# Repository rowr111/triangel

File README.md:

# Triangel!

ART!!! Made of 25 triangle tiles and 600 LEDs, for a wall or the corner of a room, with pleasing ambient patterns and exciting audio-reactive patterns specially tuned to follow music.

<table align="center">
  <tr>
    <td align="center"><br>Flame</td>
    <td align="center"><br>Uzumaki</td>
    <td align="center"><br>Fubuki</td>
    <td align="center"><br>Raindrop (sound)</td>
    <td align="center"><br>Spectrum (sound)</td>
  </tr>
</table>

- 50 cm per side when assembled
- 14 patterns: slow ambient ones, and ones that move with the beat, the drops and the shape of the music
- Audio-reactive mode: set on/off or auto-detected when music is playing
- Controlled by: buttons, a sound switch or a remote; no app/connected computer needed
- Open source: the circuit boards, the brackets and the firmware are all here, in Rust, on two [dabao](https://www.crowdsupply.com/baochip/dabao) boards using the [Baochip-1x](https://github.com/baochip/baochip-1x), running [Xous](https://github.com/betrusted-io/xous-core)

You don't need a Triangel to write patterns for it: one dabao board and a browser will do. [Start here](docs/tutorials/first-run.md).

## Why the name?

Each triangle tile has a stylized eye design in the middle.. After I decided to cover it in eyes, I was inspired by biblical angel descriptions to name it... triangle + angel = Triangel!

## Where to go

### If you have a Triangel

- [Use your Triangel](USER_GUIDE.md#controls): the controls
- [Update its firmware](docs/how-to/update-your-triangel.md)

### If you want to build your own

- [How to build a Triangel](docs/how-to/build-a-triangel.md): everything you need, and how to put it together
  - [How to manufacture the circuit boards](docs/how-to/manufacture-the-circuit-boards.md)
  - [How to order the six-way and three-way brackets](docs/how-to/order-the-brackets.md)
  - [How to order the frame](docs/how-to/order-the-frame.md)
  - [How to order the wall brackets](docs/how-to/order-the-wall-brackets.md)
  - [How to order the controller board enclosure](docs/how-to/order-the-controller-board-enclosure.md)
  - [Print the stickers and overlays](graphics/README.md)

### If you want to develop

- **Learn**
  - [Build and preview Triangel patterns with one dabao](docs/tutorials/first-run.md): start here if you are new, or don't have Triangel hardware
  - [Write your first pattern](docs/tutorials/first-pattern.md)
  - [Write a sound pattern](docs/tutorials/first-sound-pattern.md)
- **How to**
  - **Get set up**
    - [Set up your machine](docs/how-to/set-up-a-development-machine.md)
    - [Build the firmware and flash the boards](docs/how-to/build-and-flash.md)
    - [Make a dabao start by itself](docs/how-to/make-a-dabao-start-by-itself.md)
    - [Watch the patterns in a browser](docs/how-to/run-the-previewer.md)
  - **Work on patterns**
    - [Add a pattern](docs/how-to/add-a-pattern.md)
    - [Make a pattern fast enough](docs/how-to/make-a-pattern-fast-enough.md)
    - [Tune the sound response](docs/how-to/tune-the-sound-response.md)
  - **Hardware and the deeper parts**
    - [Check a microphone that is not working](docs/how-to/check-the-microphone.md)
    - [Change the microphone's pins](docs/how-to/regenerate-the-mic-program.md)
    - [Regenerate the LED map](docs/how-to/regenerate-the-led-map.md)
    - [Build the kernels](docs/how-to/build-the-kernels.md)
- **Understand**
  - [How Triangel works](docs/explanation/how-triangel-works.md): the parts, the two boards, a frame, the setlists and the kernel
  - [How sound becomes light](docs/explanation/how-sound-becomes-light.md): from the microphone, through the 24 bands, to beats and drops
- **Look things up**
  - [Pattern toolkit](docs/reference/pattern-toolkit.md): the helpers, the measurements and the sound
  - [Triangle tiles and wiring](docs/reference/triangle-tiles-and-wiring.md): the layout, the numbering and the two chains
  - [Pins](docs/reference/pins.md): which dabao pins each board uses
  - [The ear-to-eye link](docs/reference/ear-to-eye-link.md): the frames the ear sends, byte by byte
  - [Diagnostic output](docs/reference/diagnostic-output.md): the status lines the eye and the ear can print, for troubleshooting
  - [Contributing](CONTRIBUTING.md)

## What is in this repository

| Folder | Contents |
|---|---|
| [`firmware/eye/`](firmware/eye/) | The eye's firmware: LED output, patterns, controls |
| [`firmware/ear/`](firmware/ear/) | The ear's firmware: microphone, frequency bands, the link to the eye |
| [`firmware/shared/`](firmware/shared/) | Code both use: the format of what the ear sends, and the sound tuning |
| [`triangel-previewer/`](triangel-previewer/) | Shows the eye's LED output in a browser |
| [`hardware/`](hardware/) | The circuit boards (KiCad) and the brackets |
| [`graphics/`](graphics/README.md) | Artwork and the sticker sheets |

## License

MIT. See [LICENSE](LICENSE).

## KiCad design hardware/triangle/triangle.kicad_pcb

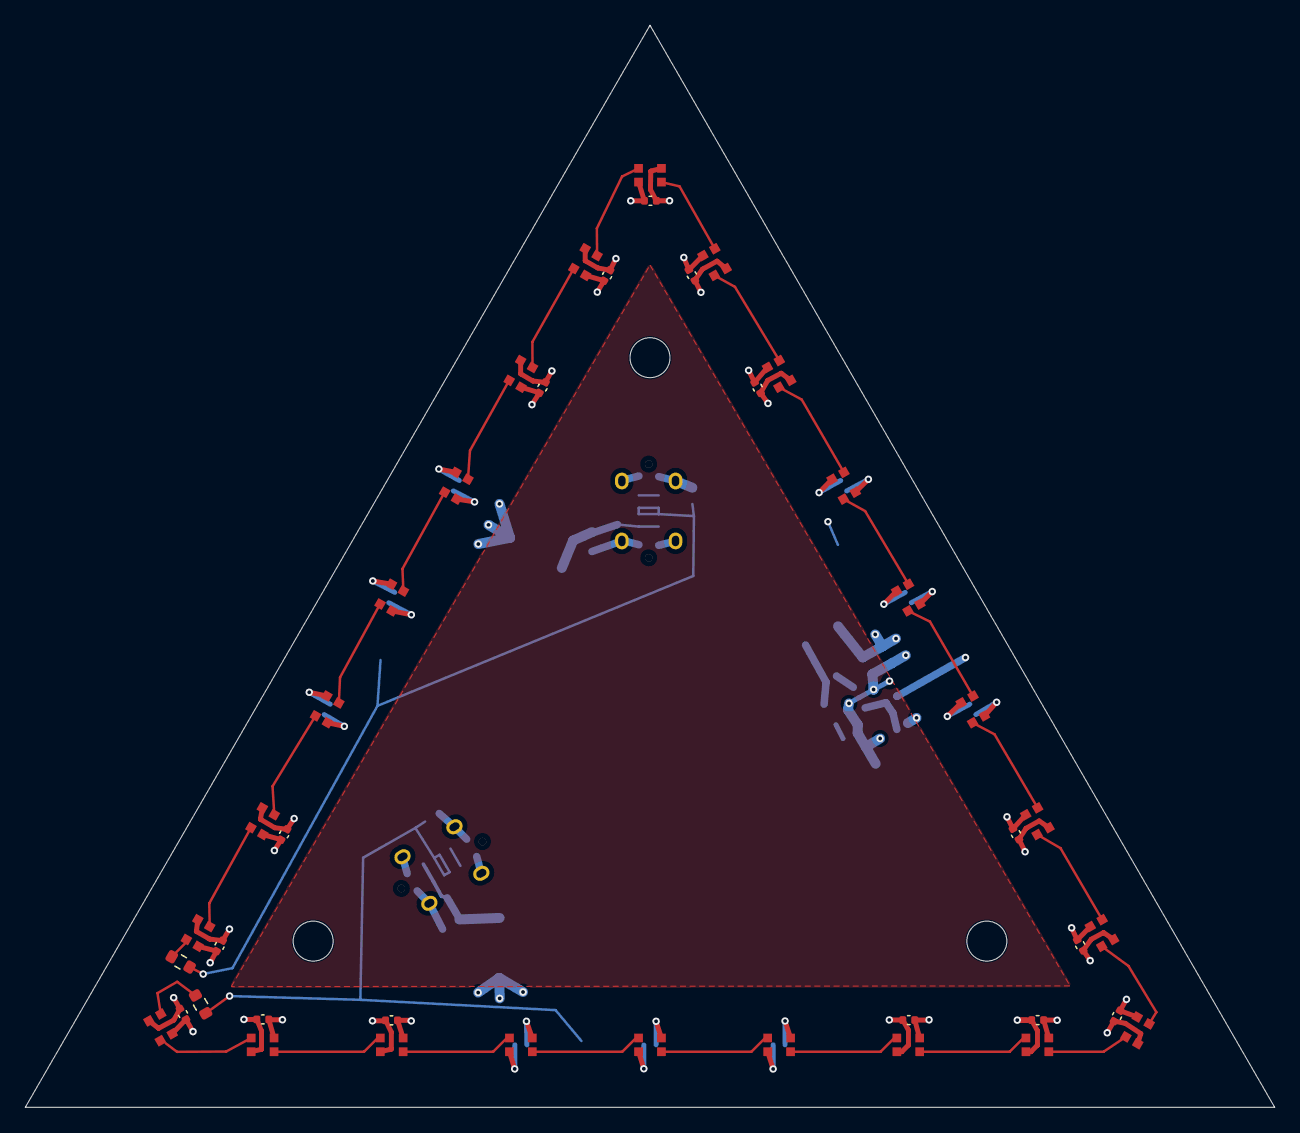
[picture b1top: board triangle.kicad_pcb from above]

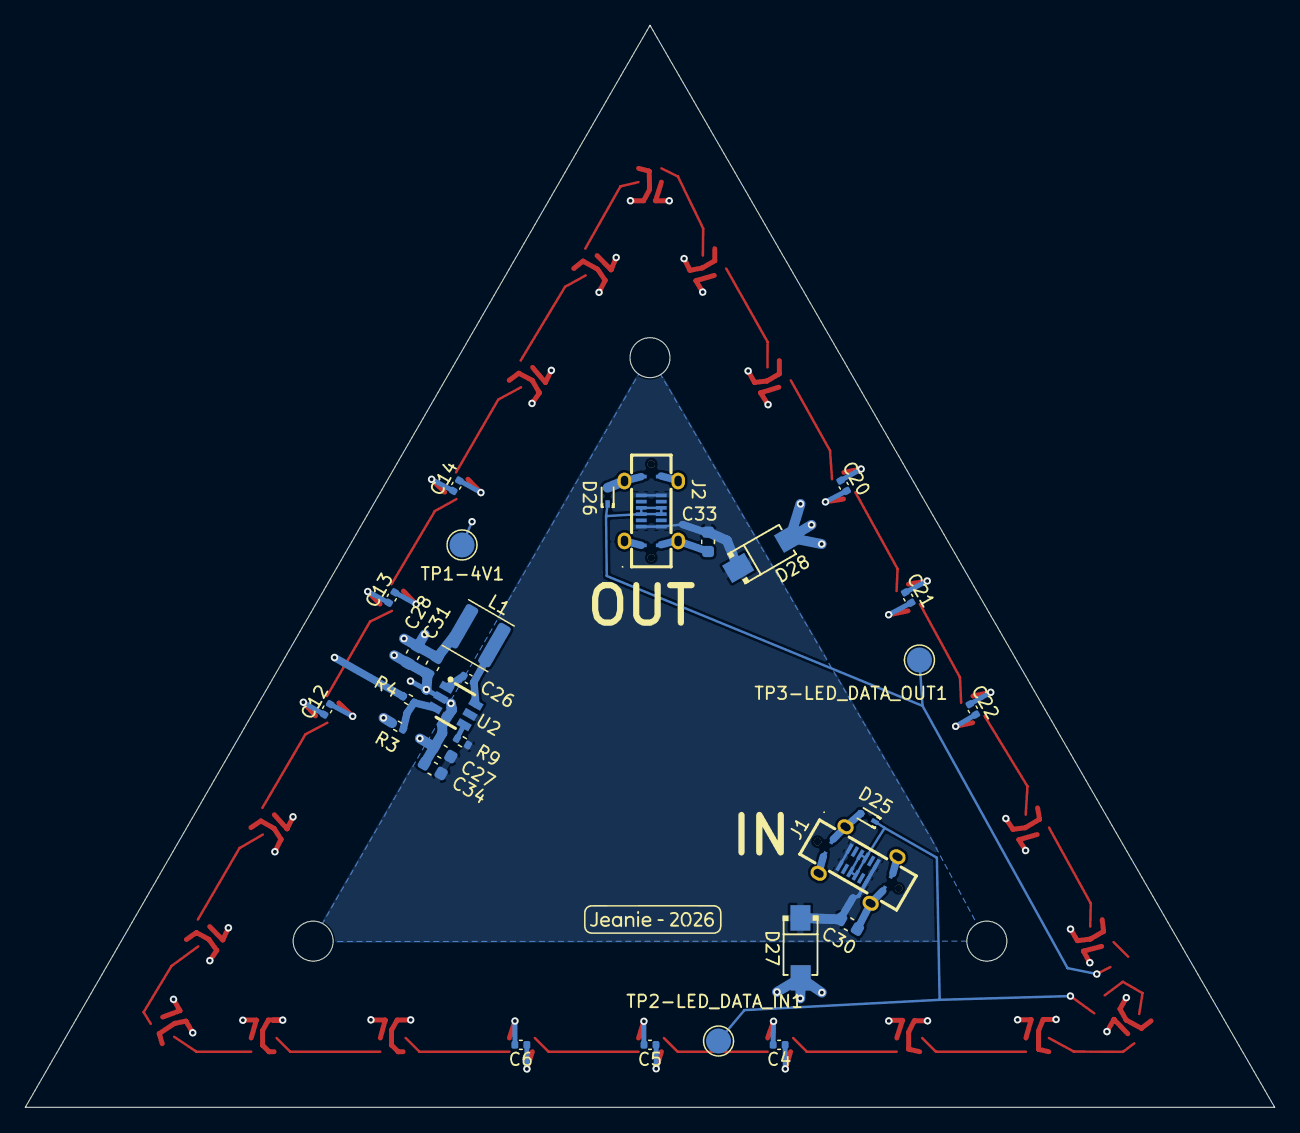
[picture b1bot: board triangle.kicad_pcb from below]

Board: 4 copper layers, 100.0 x 86.6 mm, 74 parts (30 on the bottom side), 34 nets.

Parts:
C1, C2, C3, C4, C5, C6, C7, C8, C9, C10, C11, C12, C13, C14, C15, C16, C17, C18, C19, C20, C21, C22, C23, C24: 100nF; C_0402_1005Metric
C26: 33nF; C_0402_1005Metric
C27, C28, C30, C31, C33, C34: 10µF; C_0603_1608Metric
D1, D2, D3, D4, D5, D6, D7, D8, D9, D10, D11, D12, D13, D14, D15, D16, D17, D18, D19, D20, D21, D22, D23, D24: WS2812B-2020; LED_WS2812B-2020_PLCC4_2.0x2.0mm - no silkscreen
D25, D26: H5VUD5U_C20617921; SOD-523_L1.2-W0.8-LS1.6-RD
D27, D28: SMAJ15A_C19077535; SMA_L4.3-W2.6-LS5.0-RD
H1, H2, H3: MountingHole; MountingHole_3.2mm_M3
J1, J2: USB_C_Receptacle_USB2.0_16P; TYPE-C-SMD_USB4120-03-C
L1: 4.7uH; L_Changjiang_FNR4030S
R1, R2: 33Ω; R_0603_1608Metric
R3, R9: 100kΩ; R_0402_1005Metric
R4: 560kΩ; R_0402_1005Metric
TP1-4V1, TP2-LED_DATA_IN1, TP3-LED_DATA_OUT1: TestPoint; TestPoint_Pad_D2.0mm
U2: EA8212HT6R; SOT-23-6_L2.9-W1.6-P0.95-LS2.8-BR

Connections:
+4V: C1.1, C2.1, C3.1, C4.1, C5.1, C6.1, C7.1, C8.1, C9.1, C10.1, C11.1, C12.1, C13.1, C14.1, C15.1, C16.1, C17.1, C18.1, C19.1, C20.1, C21.1, C22.1, C23.1, C24.1, C28.1, C31.1, D1.4 (VDD), D2.4 (VDD), D3.4 (VDD), D4.4 (VDD), D5.4 (VDD), D6.4 (VDD), D7.4 (VDD), D8.4 (VDD), D9.4 (VDD), D10.4 (VDD), D11.4 (VDD), D12.4 (VDD), D13.4 (VDD), D14.4 (VDD), D15.4 (VDD), D16.4 (VDD), D17.4 (VDD), D18.4 (VDD), D19.4 (VDD), D20.4 (VDD), D21.4 (VDD), D22.4 (VDD), D23.4 (VDD), D24.4 (VDD), L1.2, R4.2, TP1-4V1.1 (1_1)
+12V: C27.1, C30.1, C33.1, C34.1, D27.1 (K), D28.1 (K), J1.A4 (VBUS), J1.A9 (VBUS), J1.B4 (VBUS), J1.B9 (VBUS), J2.A4 (VBUS), J2.A9 (VBUS), J2.B4 (VBUS), J2.B9 (VBUS), R9.2, U2.5 (PWR)
GND: C1.2, C2.2, C3.2, C4.2, C5.2, C6.2, C7.2, C8.2, C9.2, C10.2, C11.2, C12.2, C13.2, C14.2, C15.2, C16.2, C17.2, C18.2, C19.2, C20.2, C21.2, C22.2, C23.2, C24.2, C27.2, C28.2, C30.2, C31.2, C33.2, C34.2, D1.2 (VSS), D2.2 (VSS), D3.2 (VSS), D4.2 (VSS), D5.2 (VSS), D6.2 (VSS), D7.2 (VSS), D8.2 (VSS), D9.2 (VSS), D10.2 (VSS), D11.2 (VSS), D12.2 (VSS), D13.2 (VSS), D14.2 (VSS), D15.2 (VSS), D16.2 (VSS), D17.2 (VSS), D18.2 (VSS), D19.2 (VSS), D20.2 (VSS), D21.2 (VSS), D22.2 (VSS), D23.2 (VSS), D24.2 (VSS), D25.2 (A), D26.2 (A), D27.2 (A), D28.2 (A), J1.0 (EH), J1.A1 (GND), J1.A12 (GND), J1.B1 (GND), J1.B12 (GND), J2.0 (EH), J2.A1 (GND), J2.A12 (GND), J2.B1 (GND), J2.B12 (GND), R3.2, U2.2 (GND)
LED_DATA_IN: D25.1 (C), J1.A6 (DP1), J1.A7 (DN1), J1.B6 (DP2), J1.B7 (DN2), R1.1, TP2-LED_DATA_IN1.1 (1_1)
LED_DATA_OUT: D26.1 (C), J2.A6 (DP1), J2.A7 (DN1), J2.B6 (DP2), J2.B7 (DN2), R2.2, TP3-LED_DATA_OUT1.1 (1_1)
unnamed: D1.3 (DIN), R1.2
unnamed: D1.1 (DOUT), D2.3 (DIN)
unnamed: D2.1 (DOUT), D3.3 (DIN)
unnamed: D3.1 (DOUT), D4.3 (DIN)
unnamed: D4.1 (DOUT), D5.3 (DIN)
unnamed: D5.1 (DOUT), D6.3 (DIN)
unnamed: D6.1 (DOUT), D7.3 (DIN)
unnamed: D7.1 (DOUT), D8.3 (DIN)
unnamed: D8.1 (DOUT), D9.3 (DIN)
unnamed: D9.1 (DOUT), D10.3 (DIN)
unnamed: D10.1 (DOUT), D11.3 (DIN)
unnamed: D11.1 (DOUT), D12.3 (DIN)
unnamed: D12.1 (DOUT), D13.3 (DIN)
unnamed: D13.1 (DOUT), D14.3 (DIN)
unnamed: D14.1 (DOUT), D15.3 (DIN)
unnamed: D15.1 (DOUT), D16.3 (DIN)
unnamed: D16.1 (DOUT), D17.3 (DIN)
unnamed: D17.1 (DOUT), D18.3 (DIN)
unnamed: D18.1 (DOUT), D19.3 (DIN)
unnamed: D19.1 (DOUT), D20.3 (DIN)
unnamed: D20.1 (DOUT), D21.3 (DIN)
unnamed: D21.1 (DOUT), D22.3 (DIN)
unnamed: D22.1 (DOUT), D23.3 (DIN)
unnamed: D23.1 (DOUT), D24.3 (DIN)
unnamed: D24.1 (DOUT), R2.1
unnamed: C26.1, U2.1 (BOOT)
unnamed: R3.1, R4.1, U2.3 (FBK)
unnamed: R9.1, U2.4 (RUN)
unnamed: C26.2, L1.1, U2.6 (SWITCH)

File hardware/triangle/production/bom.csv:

Designator,Footprint,Quantity,Value,LCSC Part #
"C1, C10, C11, C12, C13, C14, C15, C16, C17, C18, C19, C2, C20, C21, C22, C23, C24, C3, C4, C5, C6, C7, C8, C9",0402,24,100nF,C1525
C26,0402,1,33nF,C507072
"C27, C28, C30, C31, C33, C34",0603,6,10µF,C96446
"D1, D10, D11, D12, D13, D14, D15, D16, D17, D18, D19, D2, D20, D21, D22, D23, D24, D3, D4, D5, D6, D7, D8, D9",LED_WS2812B-2020_PLCC4_2.0x2.0mm - no silkscreen,24,WS2812B-2020,C52917434
"D25, D26",SOD-523_L1.2-W0.8-LS1.6-RD,2,H5VUD5U_C20617921,C20617921
"D27, D28",SMA_L4.3-W2.6-LS5.0-RD,2,SMAJ15A_C19077535,C19077535
"J1, J2",TYPE-C-SMD_USB4120-03-C,2,USB_C_Receptacle_USB2.0_16P,C3151749
L1,L_Changjiang_FNR4030S,1,4.7uH,C167874
"R1, R2",0603,2,33Ω,C23140
"R3, R9",0402,2,100kΩ,C60491
R4,0402,1,560kΩ,C132339
U2,SOT-23-6_L2.9-W1.6-P0.95-LS2.8-BR,1,EA8212HT6R,C609568

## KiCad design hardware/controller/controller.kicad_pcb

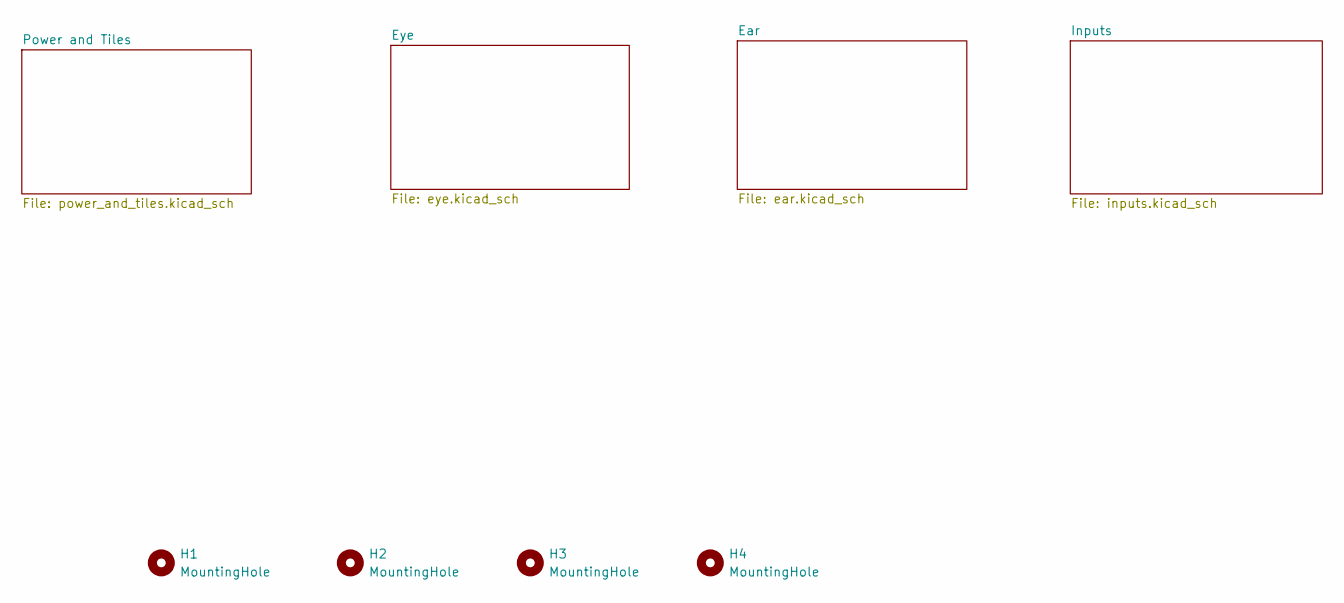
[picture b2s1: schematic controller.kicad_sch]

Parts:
H1, H2, H3, H4: MountingHole; MountingHole_3.2mm_M3_Pad

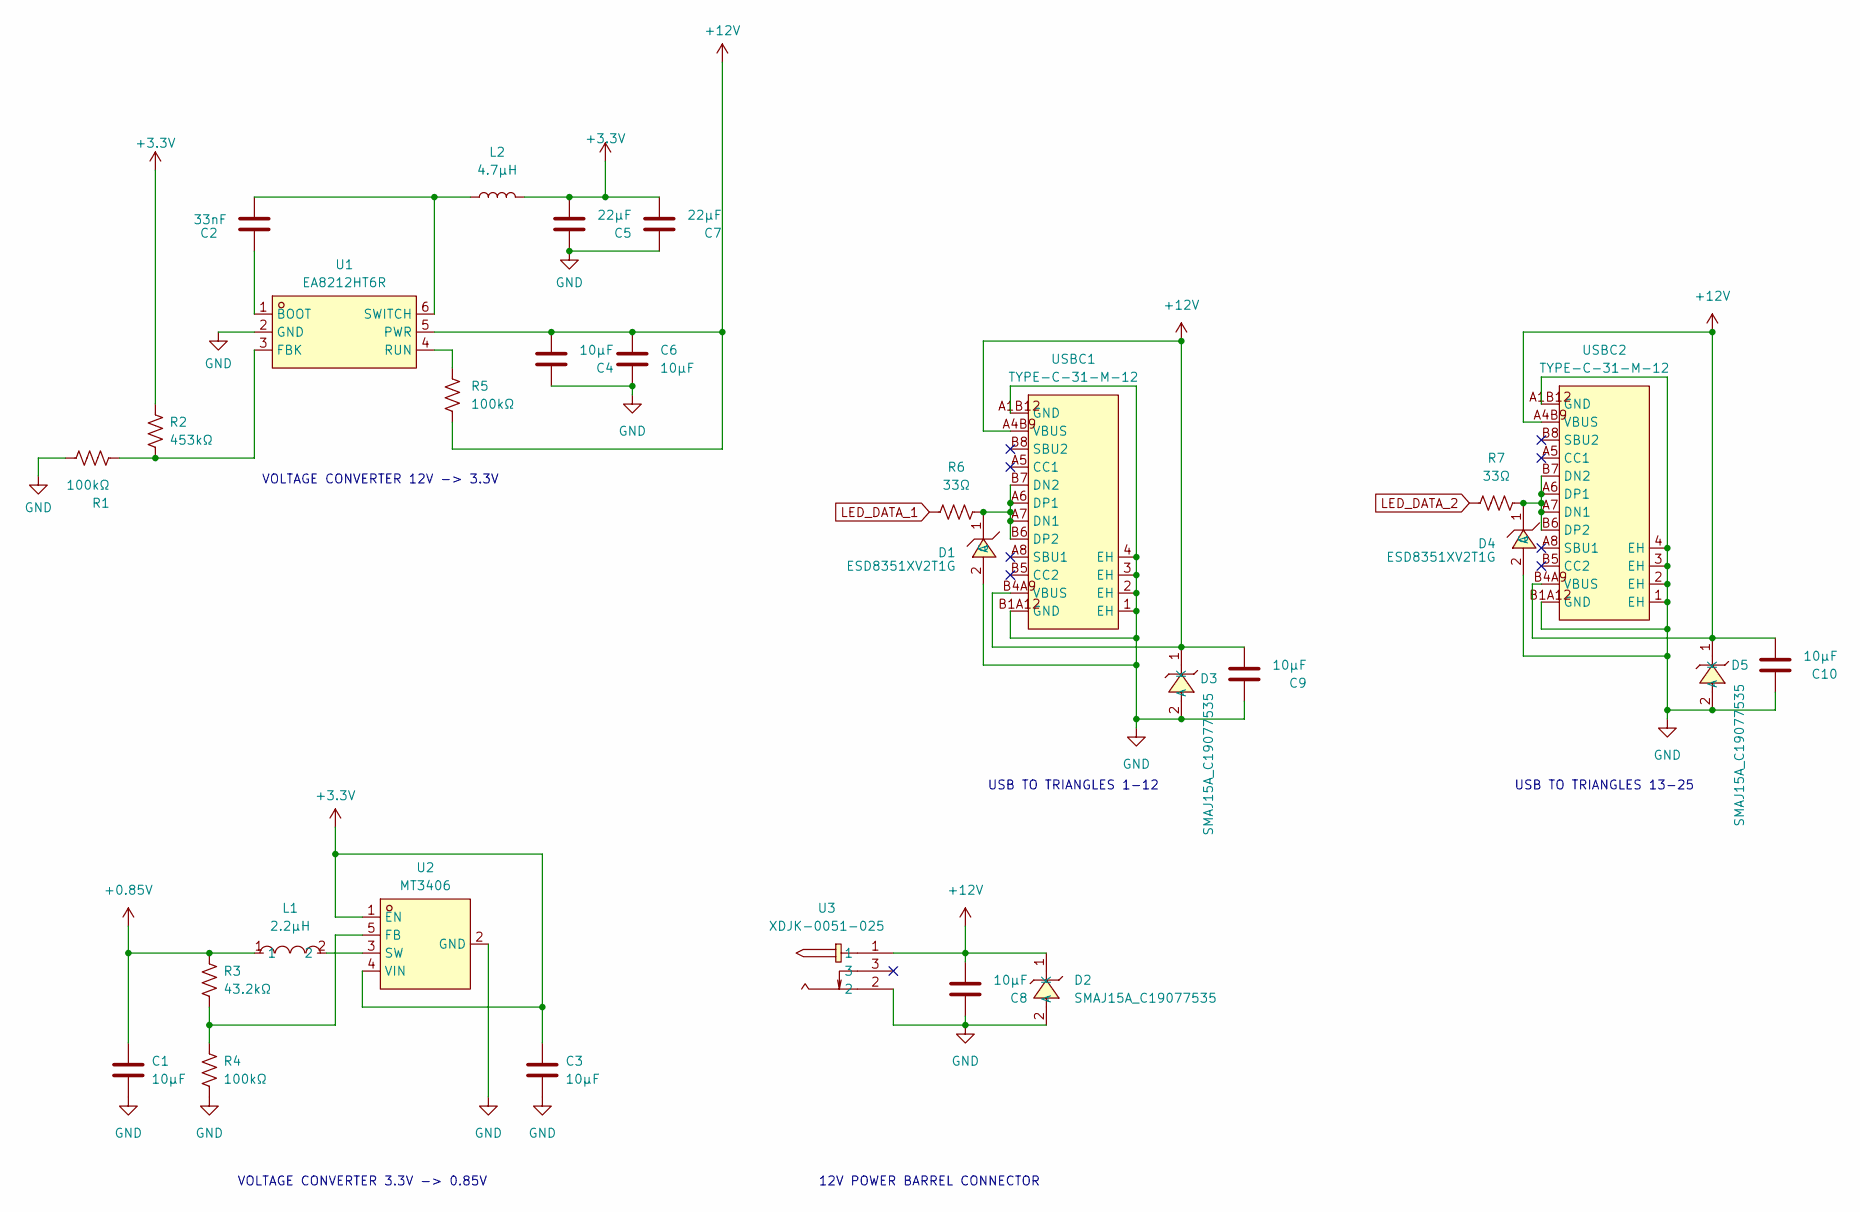
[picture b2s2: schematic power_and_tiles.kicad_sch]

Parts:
C1, C3, C4, C6, C8, C9, C10: 10µF; C_0603_1608Metric; LCSC Part C96446
C2: 33nF; C_0402_1005Metric; LCSC Part C507072
C5, C7: 22µF; C_0805_2012Metric; LCSC Part C45783
D1, D4: ESD8351XV2T1G; SOD-523_L1.2-W0.8-LS1.6-RD; MPN ESD8351XV2T1G; LCSC Part C19829478
D2, D3, D5: SMAJ15A_C19077535; SMA_L4.3-W2.6-LS5.0-RD; MPN SMAJ15A; LCSC Part C19077535
L1: 2.2µH; L0805; MPN MGFL2012F2R2MT-LF; LCSC Part C281115
L2: 4.7µH; L_Changjiang_FNR4030S; MPN FNR4030S4R7MT; LCSC Part C167874
R1, R4, R5: 100kΩ; R_0402_1005Metric; LCSC Part C60491
R2: 453kΩ; R_0402_1005Metric; LCSC Part C27009
R3: 43.2kΩ; R_0402_1005Metric; LCSC Part C25894
R6, R7: 33Ω; R_0402_1005Metric; LCSC Part C25105
U1: EA8212HT6R; SOT-23-6_L2.9-W1.6-P0.95-LS2.8-BR; MPN EA8212HT6R; LCSC Part C609568
U2: MT3406; SOT-23-5; MPN MT3406; LCSC Part C22462728
U3: XDJK-0051-025; DC-IN-TH_XDJK-0051-025; MPN XDJK-0051-025; LCSC Part C7498153
USBC1, USBC2: TYPE-C-31-M-12; USB-C_SMD-TYPE-C-31-M-12_1; MPN TYPE-C-31-M-12; LCSC Part C165948

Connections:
+0.85V: C1.1, L1.1, R3.1; also elsewhere on the board
+3.3V: C3.1, C5.1, C7.1, L2.2, R2.2, U2.1 (EN), U2.4 (VIN); also elsewhere on the board
+12V: C4.1, C6.1, C8.1, C9.1, C10.1, D2.1 (K), D3.1 (K), D5.1 (K), R5.2, U1.5 (PWR), U3.1, USBC1.A4B9 (VBUS), USBC1.B4A9 (VBUS), USBC2.A4B9 (VBUS), USBC2.B4A9 (VBUS)
GND: C1.2, C3.2, C4.2, C5.2, C6.2, C7.2, C8.2, C9.2, C10.2, D1.2 (A), D2.2 (A), D3.2 (A), D4.2 (A), D5.2 (A), R1.2, R4.2, U1.2 (GND), U2.2 (GND), U3.2, USBC1.1 (EH), USBC1.2 (EH), USBC1.3 (EH), USBC1.4 (EH), USBC1.A1B12 (GND), USBC1.B1A12 (GND), USBC2.1 (EH), USBC2.2 (EH), USBC2.3 (EH), USBC2.4 (EH), USBC2.A1B12 (GND), USBC2.B1A12 (GND); also elsewhere on the board
LED_DATA_1: R6.1; also elsewhere on the board
LED_DATA_2: R7.1; also elsewhere on the board
unnamed: D1.1 (C), R6.2, USBC1.A6 (DP1), USBC1.A7 (DN1), USBC1.B6 (DP2), USBC1.B7 (DN2)
unnamed: D4.1 (C), R7.2, USBC2.A6 (DP1), USBC2.A7 (DN1), USBC2.B6 (DP2), USBC2.B7 (DN2)
unnamed: C2.1, U1.1 (BOOT)
unnamed: R1.1, R2.1, U1.3 (FBK)
unnamed: R5.1, U1.4 (RUN)
unnamed: C2.2, L2.1, U1.6 (SWITCH)
unnamed: R3.2, R4.1, U2.5 (FB)
unnamed: L1.2, U2.3 (SW)

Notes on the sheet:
USB TO TRIANGLES 13-25
VOLTAGE CONVERTER 3.3V -> 0.85V
12V POWER BARREL CONNECTOR
VOLTAGE CONVERTER 12V -> 3.3V
USB TO TRIANGLES 1-12

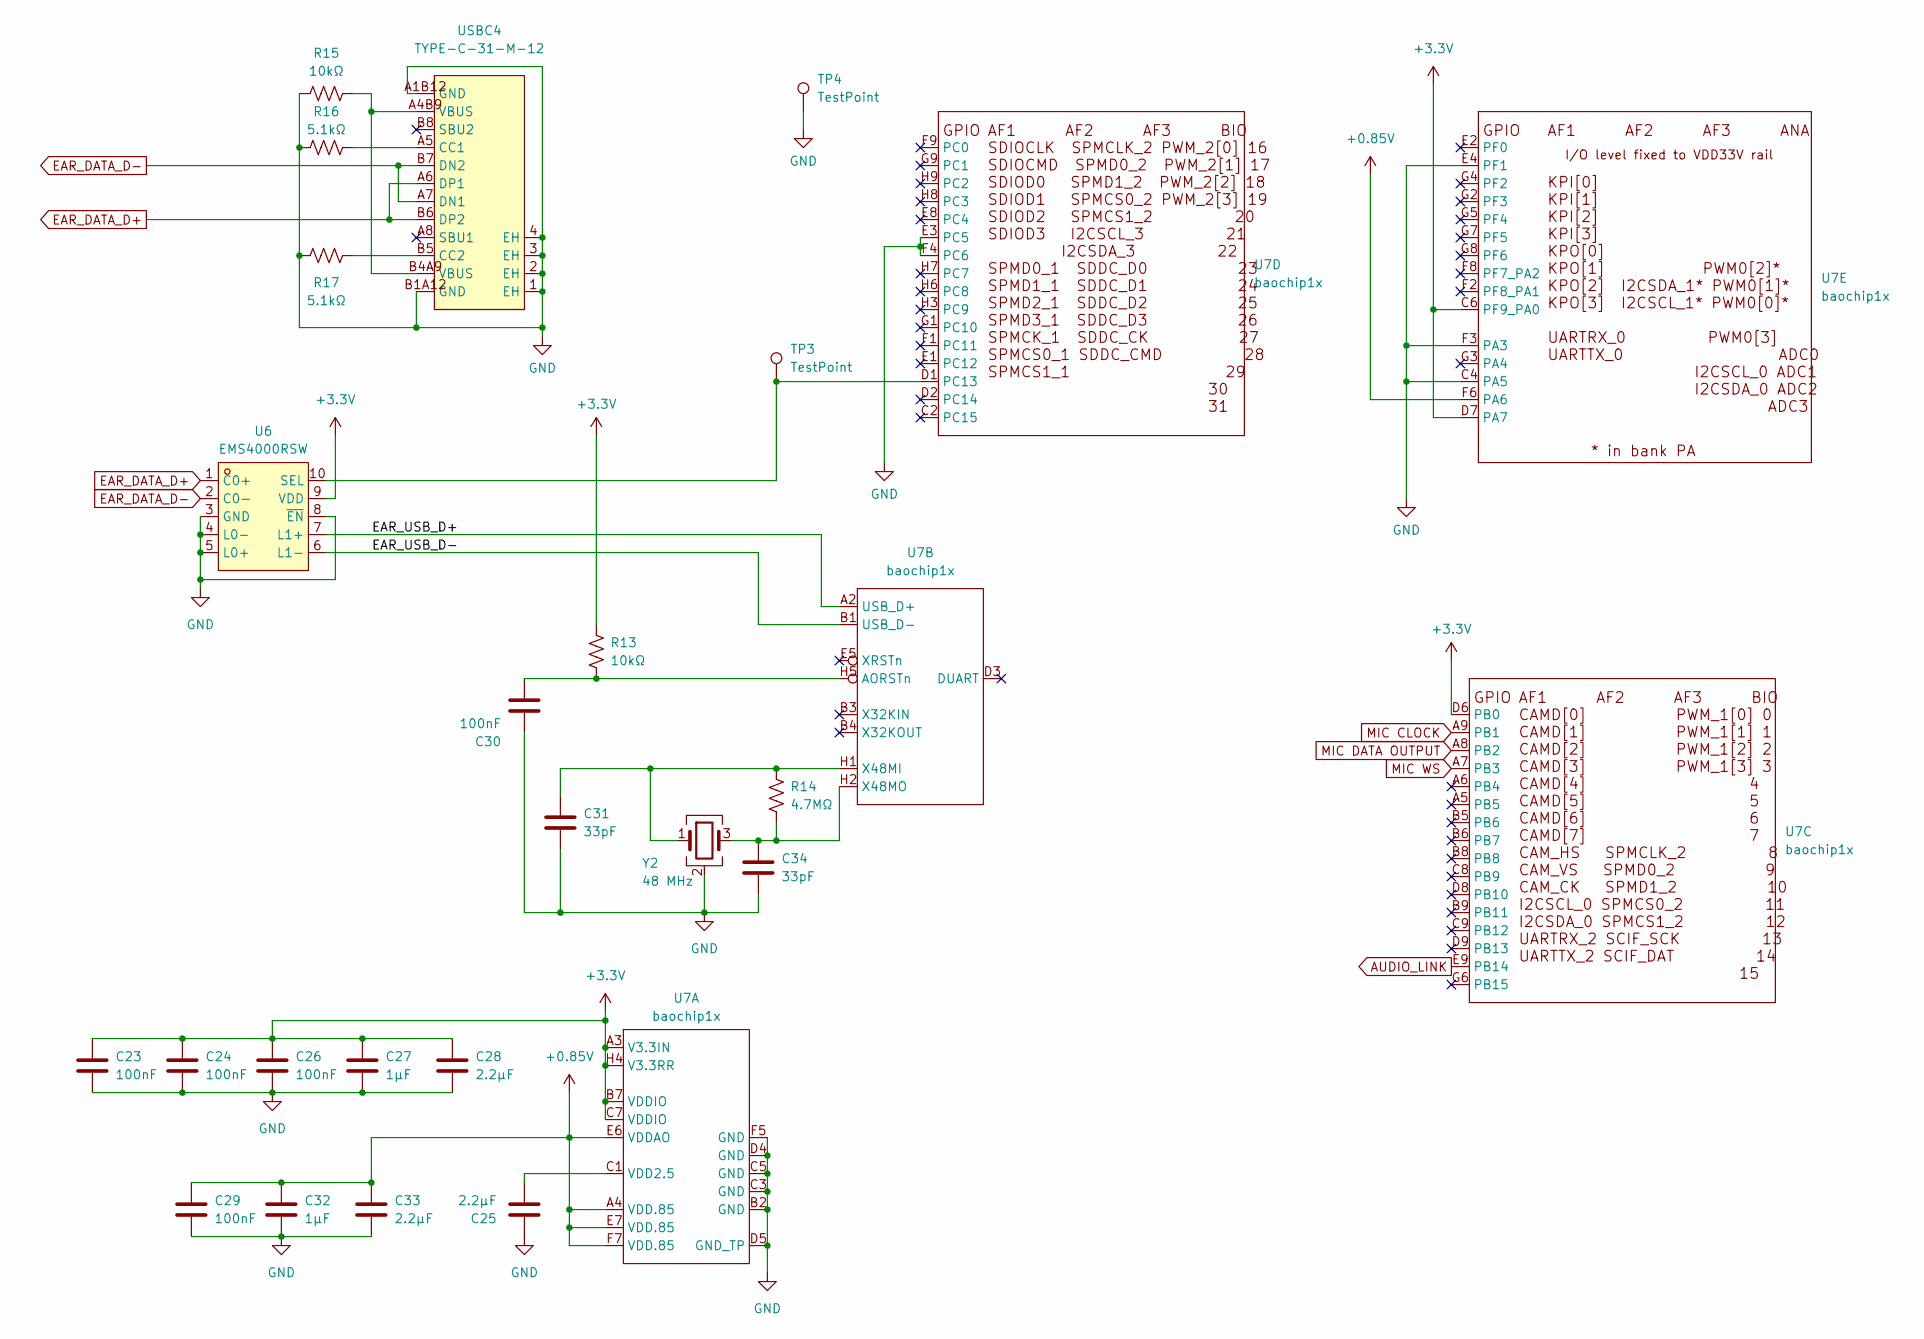
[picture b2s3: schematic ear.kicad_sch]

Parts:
C23, C24, C26, C29, C30: 100nF; C_0201_0603Metric; LCSC Part C76934
C25, C28, C33: 2.2µF; C_0201_0603Metric; LCSC Part C76933
C27, C32: 1µF; C_0201_0603Metric; LCSC Part C76935
C31, C34: 33pF; C_0201_0603Metric; LCSC Part C56903
R13: 10kΩ; R_0201_0603Metric; LCSC Part C106225
R14: 4.7MΩ; R_0402_1005Metric; LCSC Part C474132
R15: 10kΩ; R_0402_1005Metric; LCSC Part C25744
R16, R17: 5.1kΩ; R_0402_1005Metric; LCSC Part C25905
TP3, TP4: TestPoint; TestPoint_Pad_D1.0mm
U6: EMS4000RSW; UQFN-10_L1.8-W1.4-P0.40-TL; MPN EMS4000RSW; LCSC Part C49186227
U7: baochip1x; WLCSP-71_9x8_4.062x3.762mm
USBC4: TYPE-C-31-M-12; USB-C_SMD-TYPE-C-31-M-12_1; MPN TYPE-C-31-M-12; LCSC Part C165948
Y2: 48 MHz; Crystal_SMD_3225-4Pin_3.2x2.5mm; LCSC Part C2892060

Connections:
+0.85V: C29.1, C32.1, C33.1, U7.A4 (VDD.85), U7.E6 (VDDAO), U7.E7 (VDD.85), U7.F6 (PA6), U7.F7 (VDD.85); also elsewhere on the board
+3.3V: C23.1, C24.1, C26.1, C27.1, C28.1, R13.1, U6.9 (VDD), U7.A3 (V3.3IN), U7.B7 (VDDIO), U7.C6 (PF9_PA0), U7.C7 (VDDIO), U7.D6 (PB0), U7.D7 (PA7), U7.H4 (V3.3RR); also elsewhere on the board
/Ear/EAR_RX: U7.D9 (PB13); also elsewhere on the board
/Ear/EAR_USB_D+: U6.7 (L1+), U7.A2 (USB_D+)
/Ear/EAR_USB_D-: U6.6 (L1-), U7.B1 (USB_D-)
AUDIO_LINK: U7.E9 (PB14); also elsewhere on the board
EAR_DATA_D+: U6.1 (C0+), USBC4.A6 (DP1), USBC4.B6 (DP2)
EAR_DATA_D-: U6.2 (C0-), USBC4.A7 (DN1), USBC4.B7 (DN2)
GND: C23.2, C24.2, C25.2, C26.2, C27.2, C28.2, C29.2, C30.2, C31.2, C32.2, C33.2, C34.2, R15.1, R16.1, R17.1, TP4.1, U6.3 (GND), U6.4 (L0-), U6.5 (L0+), U6.8 (~EN), U7.B2 (GND), U7.C3 (GND), U7.C4 (PA5), U7.C5 (GND), U7.D4 (GND), U7.D5 (GND_TP), U7.E3 (PC5), U7.E4 (PF1), U7.F3 (PA3), U7.F4 (PC6), U7.F5 (GND), USBC4.1 (EH), USBC4.2 (EH), USBC4.3 (EH), USBC4.4 (EH), USBC4.A1B12 (GND), USBC4.B1A12 (GND), Y2.2 (G), Y2.4 (G); also elsewhere on the board
MIC CLOCK: U7.A9 (PB1); also elsewhere on the board
MIC DATA OUTPUT: U7.A8 (PB2); also elsewhere on the board
MIC WS: U7.A7 (PB3); also elsewhere on the board
unnamed: R15.2, USBC4.A4B9 (VBUS), USBC4.B4A9 (VBUS)
unnamed 36: TP3.1, U6.10 (SEL), U7.D1 (PC13); also elsewhere on the board
unnamed: C25.1, U7.C1 (VDD2.5)
unnamed 48: C30.1, R13.2, U7.H5 (AORSTn); also elsewhere on the board
unnamed: C31.1, R14.1, U7.H1 (X48MI), Y2.1
unnamed: C34.1, R14.2, U7.H2 (X48MO), Y2.3
unnamed: R16.2, USBC4.A5 (CC1)
unnamed: R17.2, USBC4.B5 (CC2)

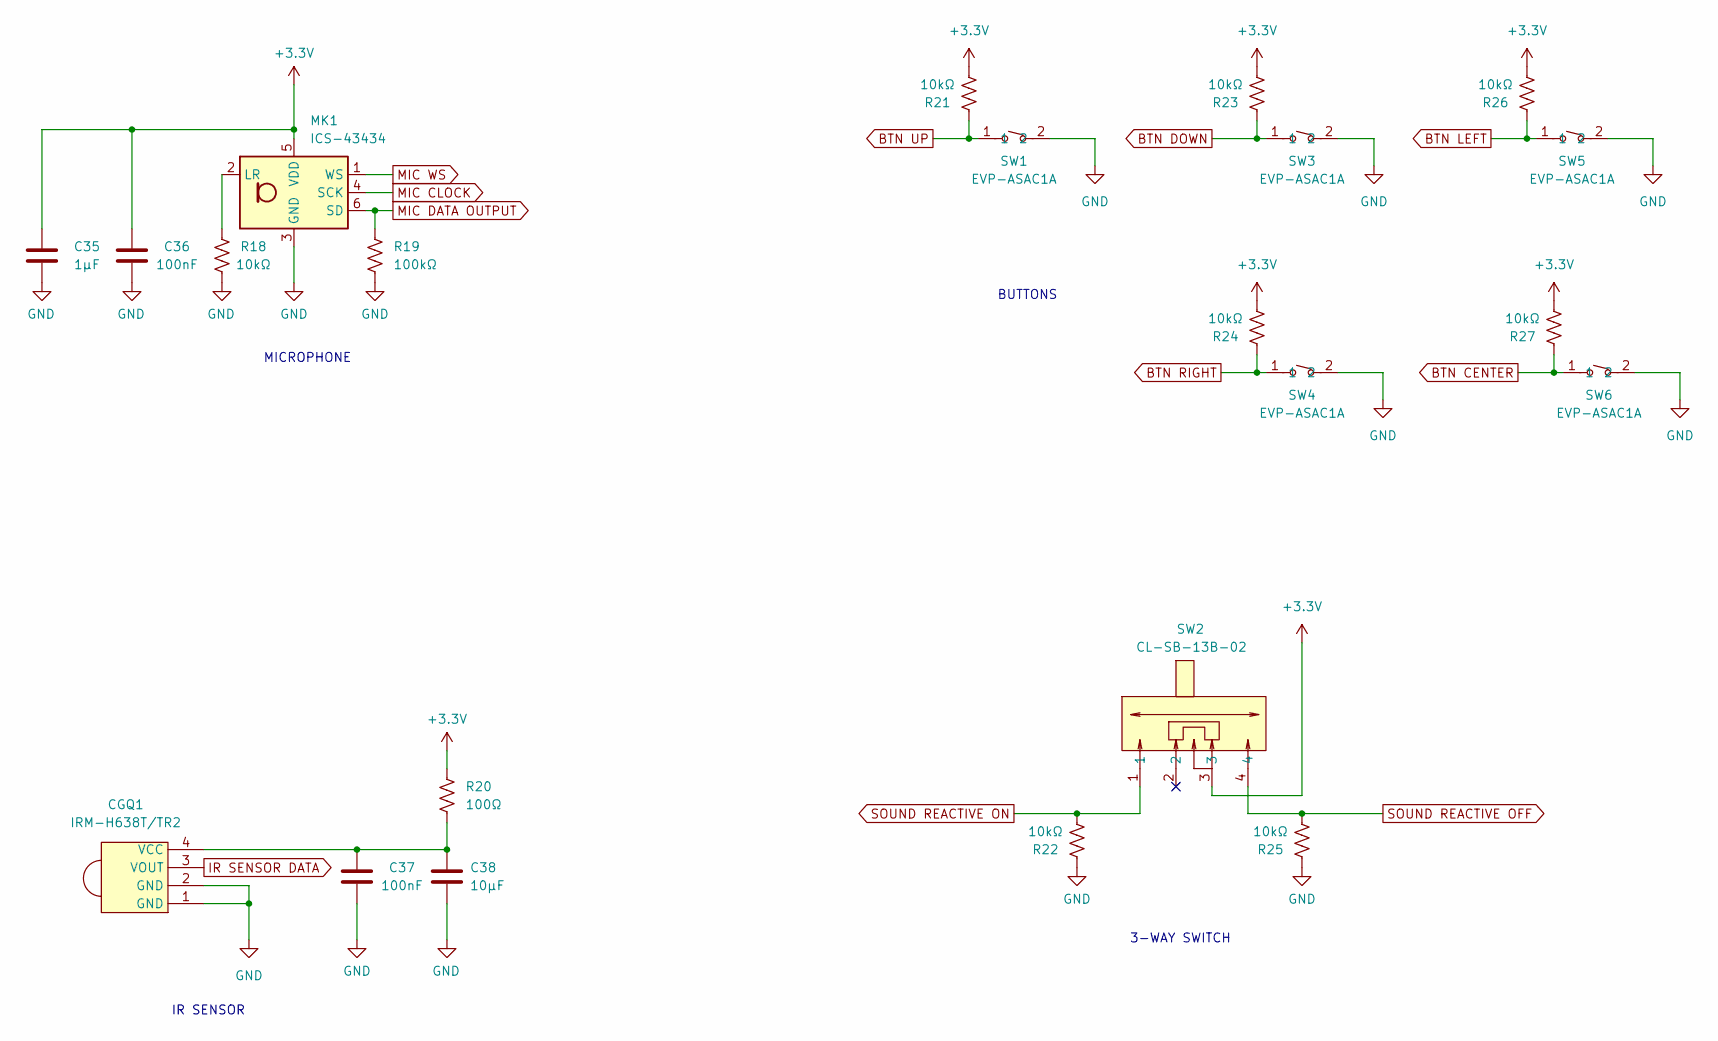
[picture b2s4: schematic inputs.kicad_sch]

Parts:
C35: 1µF; C_0402_1005Metric; LCSC Part C52923
C36, C37: 100nF; C_0402_1005Metric; LCSC Part C1525
C38: 10µF; C_0402_1005Metric; LCSC Part C15525
CGQ1: IRM-H638T/TR2; SENSOR-SMD_IRM-H638T-TR2-TL; MPN IRM-H638T/TR2; LCSC Part C91447
MK1: ICS-43434; InvenSense_ICS-43434-6_3.5x2.65mm; LCSC Part C5656610
R18, R21, R22, R23, R24, R25, R26, R27: 10kΩ; R_0402_1005Metric; LCSC Part C25744
R19: 100kΩ; R_0402_1005Metric; LCSC Part C60491
R20: 100Ω; R_0402_1005Metric; LCSC Part C25076
SW1, SW3, SW4, SW5, SW6: EVP-ASAC1A; SW-SMD_PANASONIC_EVPASXXX; MPN EVP-ASAC1A; LCSC Part C4365033
SW2: CL-SB-13B-02; SW-SMD_NIDEC_CL-SB-13B-01T; MPN CL-SB-13B-02; LCSC Part C5596339

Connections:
+3.3V: C35.1, C36.1, MK1.5 (VDD), R20.2, R21.1, R23.1, R24.1, R26.1, R27.1, SW2.3; also elsewhere on the board
BTN CENTER: R27.2, SW6.1; also elsewhere on the board
BTN DOWN: R23.2, SW3.1; also elsewhere on the board
BTN LEFT: R26.2, SW5.1; also elsewhere on the board
BTN RIGHT: R24.2, SW4.1; also elsewhere on the board
BTN UP: R21.2, SW1.1; also elsewhere on the board
GND: C35.2, C36.2, C37.2, C38.1, CGQ1.1 (GND), CGQ1.2 (GND), MK1.3 (GND), R18.1, R19.1, R22.2, R25.2, SW1.2, SW3.2, SW4.2, SW5.2, SW6.2; also elsewhere on the board
IR SENSOR DATA: CGQ1.3 (VOUT); also elsewhere on the board
MIC CLOCK: MK1.4 (SCK); also elsewhere on the board
MIC DATA OUTPUT: MK1.6 (SD), R19.2; also elsewhere on the board
MIC WS: MK1.1 (WS); also elsewhere on the board
unnamed: C37.1, C38.2, CGQ1.4 (VCC), R20.1
unnamed: MK1.2 (LR), R18.2
SOUND REACTIVE OFF: R25.1, SW2.4; also elsewhere on the board
SOUND REACTIVE ON: R22.1, SW2.1; also elsewhere on the board

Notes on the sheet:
MICROPHONE
IR SENSOR
BUTTONS
3-WAY SWITCH

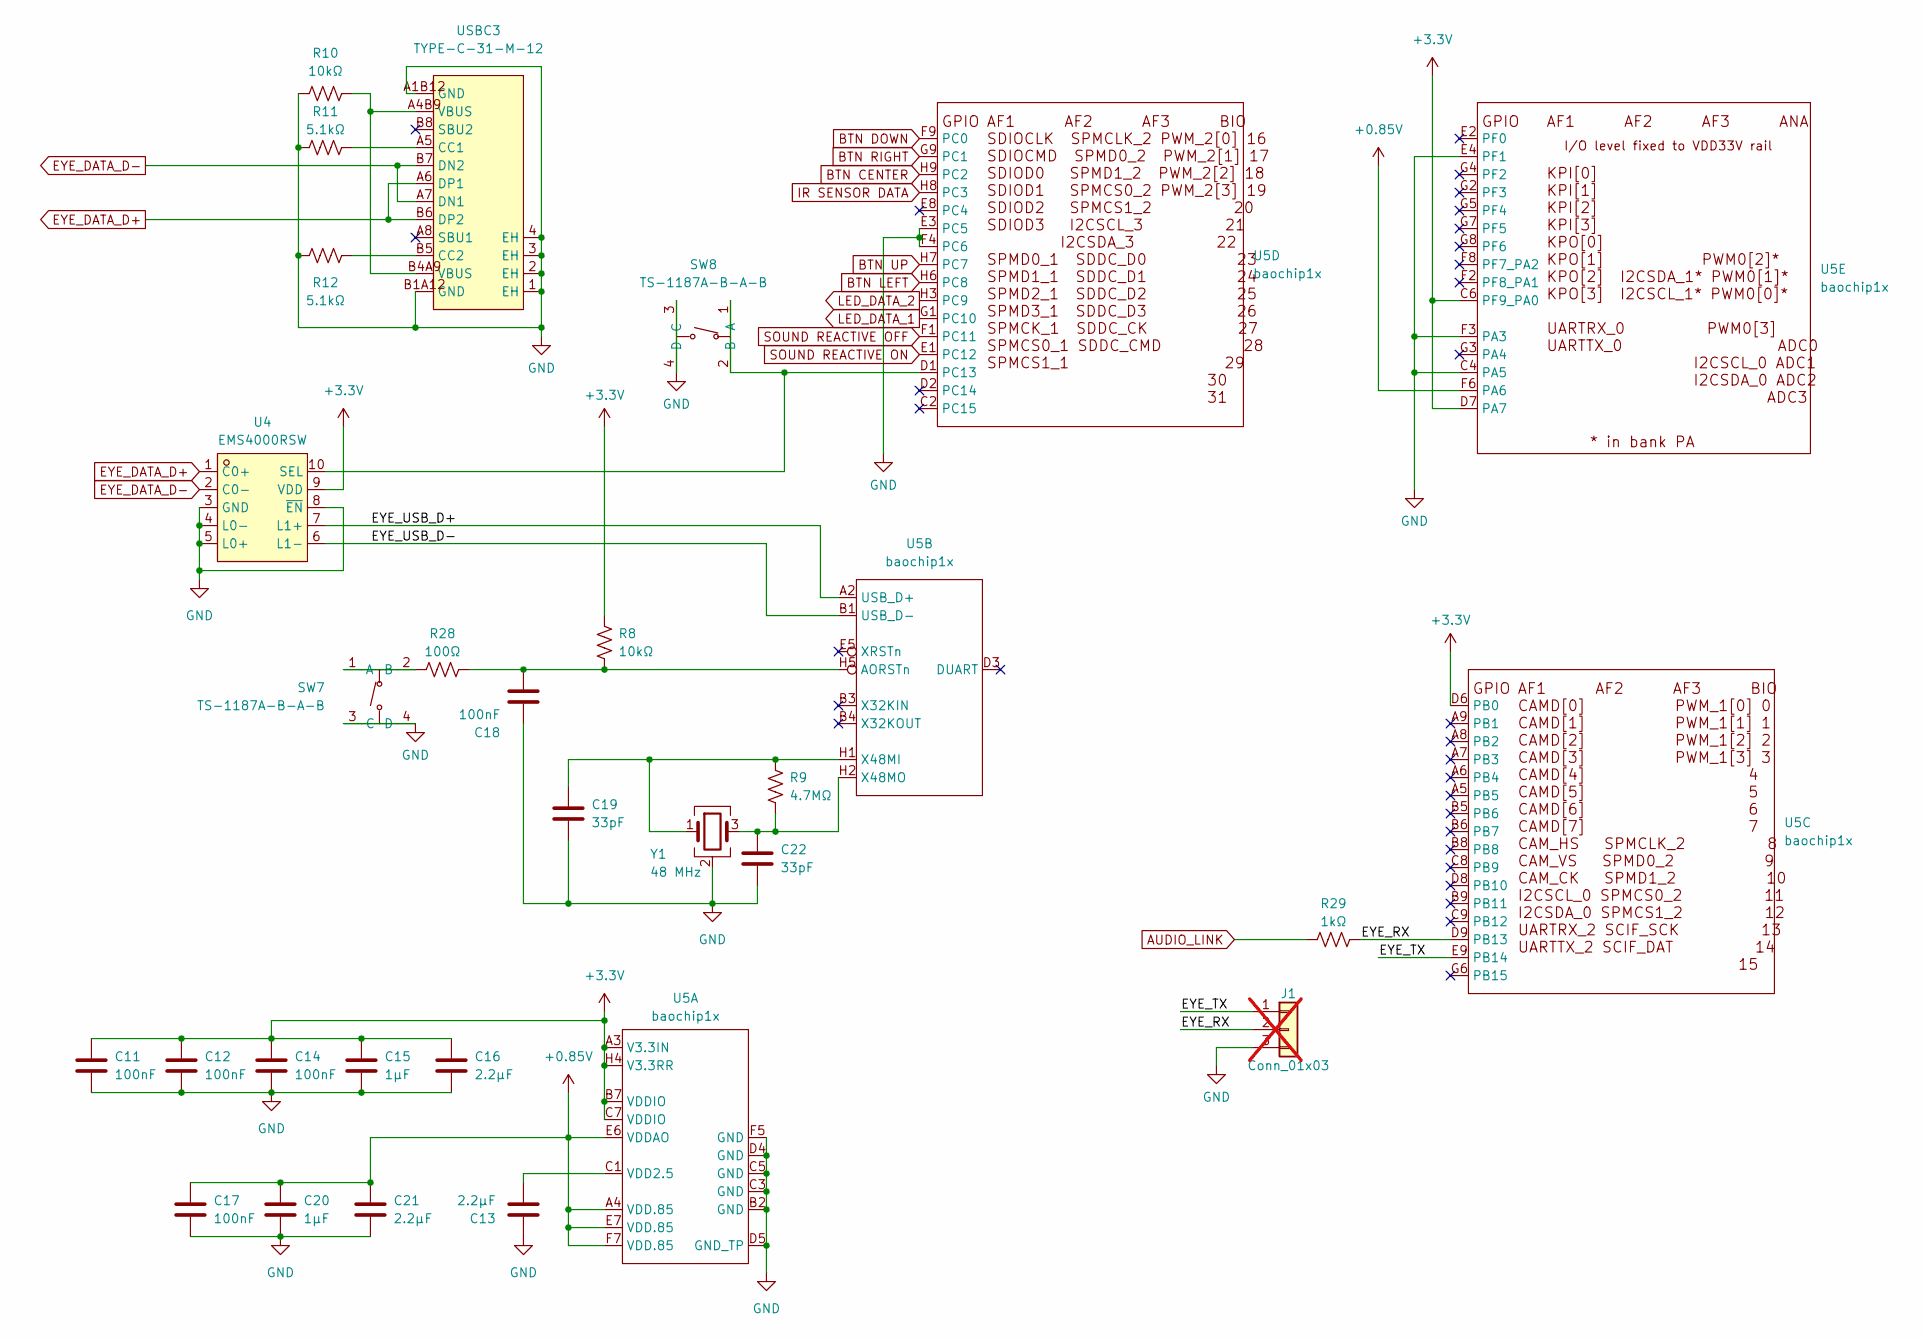
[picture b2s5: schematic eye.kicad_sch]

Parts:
C11, C12, C14, C17, C18: 100nF; C_0201_0603Metric; LCSC Part C76934
C13, C16, C21: 2.2µF; C_0201_0603Metric; LCSC Part C76933
C15, C20: 1µF; C_0201_0603Metric; LCSC Part C76935
C19, C22: 33pF; C_0201_0603Metric; LCSC Part C56903
J1: Conn_01x03; PinHeader_1x03_P2.54mm_Vertical; not fitted
R8: 10kΩ; R_0201_0603Metric; LCSC Part C106225
R9: 4.7MΩ; R_0402_1005Metric; LCSC Part C474132
R10: 10kΩ; R_0402_1005Metric; LCSC Part C25744
R11, R12: 5.1kΩ; R_0402_1005Metric; LCSC Part C25905
R28: 100Ω; R_0402_1005Metric; LCSC Part C25076
R29: 1kΩ; R_0402_1005Metric; LCSC Part C11702
SW7, SW8: TS-1187A-B-A-B; SW-SMD_4P-L5.1-W5.1-P3.70-LS6.5-TL_H1.5; MPN TS-1187A-B-A-B; LCSC Part C318884
U4: EMS4000RSW; UQFN-10_L1.8-W1.4-P0.40-TL; MPN EMS4000RSW; LCSC Part C49186227
U5: baochip1x; WLCSP-71_9x8_4.062x3.762mm
USBC3: TYPE-C-31-M-12; USB-C_SMD-TYPE-C-31-M-12_1; MPN TYPE-C-31-M-12; LCSC Part C165948
Y1: 48 MHz; Crystal_SMD_3225-4Pin_3.2x2.5mm; LCSC Part C2892060

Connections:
+0.85V: C17.1, C20.1, C21.1, U5.A4 (VDD.85), U5.E6 (VDDAO), U5.E7 (VDD.85), U5.F6 (PA6), U5.F7 (VDD.85); also elsewhere on the board
+3.3V: C11.1, C12.1, C14.1, C15.1, C16.1, R8.1, U4.9 (VDD), U5.A3 (V3.3IN), U5.B7 (VDDIO), U5.C6 (PF9_PA0), U5.C7 (VDDIO), U5.D6 (PB0), U5.D7 (PA7), U5.H4 (V3.3RR); also elsewhere on the board
/Eye/EYE_RX: J1.2, R29.2, U5.D9 (PB13)
/Eye/EYE_TX: J1.1, U5.E9 (PB14)
/Eye/EYE_USB_D+: U4.7 (L1+), U5.A2 (USB_D+)
/Eye/EYE_USB_D-: U4.6 (L1-), U5.B1 (USB_D-)
AUDIO_LINK: R29.1; also elsewhere on the board
BTN CENTER: U5.H9 (PC2); also elsewhere on the board
BTN DOWN: U5.F9 (PC0); also elsewhere on the board
BTN LEFT: U5.H6 (PC8); also elsewhere on the board
BTN RIGHT: U5.G9 (PC1); also elsewhere on the board
BTN UP: U5.H7 (PC7); also elsewhere on the board
EYE_DATA_D+: U4.1 (C0+), USBC3.A6 (DP1), USBC3.B6 (DP2)
EYE_DATA_D-: U4.2 (C0-), USBC3.A7 (DN1), USBC3.B7 (DN2)
GND: C11.2, C12.2, C13.2, C14.2, C15.2, C16.2, C17.2, C18.2, C19.2, C20.2, C21.2, C22.2, J1.3, R10.1, R11.1, R12.1, SW7.3 (C), SW7.4 (D), SW8.3 (C), SW8.4 (D), U4.3 (GND), U4.4 (L0-), U4.5 (L0+), U4.8 (~EN), U5.B2 (GND), U5.C3 (GND), U5.C4 (PA5), U5.C5 (GND), U5.D4 (GND), U5.D5 (GND_TP), U5.E3 (PC5), U5.E4 (PF1), U5.F3 (PA3), U5.F4 (PC6), U5.F5 (GND), USBC3.1 (EH), USBC3.2 (EH), USBC3.3 (EH), USBC3.4 (EH), USBC3.A1B12 (GND), USBC3.B1A12 (GND), Y1.2 (G), Y1.4 (G); also elsewhere on the board
IR SENSOR DATA: U5.H8 (PC3); also elsewhere on the board
LED_DATA_1: U5.G1 (PC10); also elsewhere on the board
LED_DATA_2: U5.H3 (PC9); also elsewhere on the board
unnamed: R10.2, USBC3.A4B9 (VBUS), USBC3.B4A9 (VBUS)
unnamed: R28.1, SW7.1 (A), SW7.2 (B)
unnamed: SW8.1 (A), SW8.2 (B), U4.10 (SEL), U5.D1 (PC13)
unnamed: C13.1, U5.C1 (VDD2.5)
unnamed: C18.1, R8.2, R28.2, U5.H5 (AORSTn)
unnamed: C19.1, R9.1, U5.H1 (X48MI), Y1.1
unnamed: C22.1, R9.2, U5.H2 (X48MO), Y1.3
unnamed: R11.2, USBC3.A5 (CC1)
unnamed: R12.2, USBC3.B5 (CC2)
SOUND REACTIVE OFF: U5.F1 (PC11); also elsewhere on the board
SOUND REACTIVE ON: U5.E1 (PC12); also elsewhere on the board
